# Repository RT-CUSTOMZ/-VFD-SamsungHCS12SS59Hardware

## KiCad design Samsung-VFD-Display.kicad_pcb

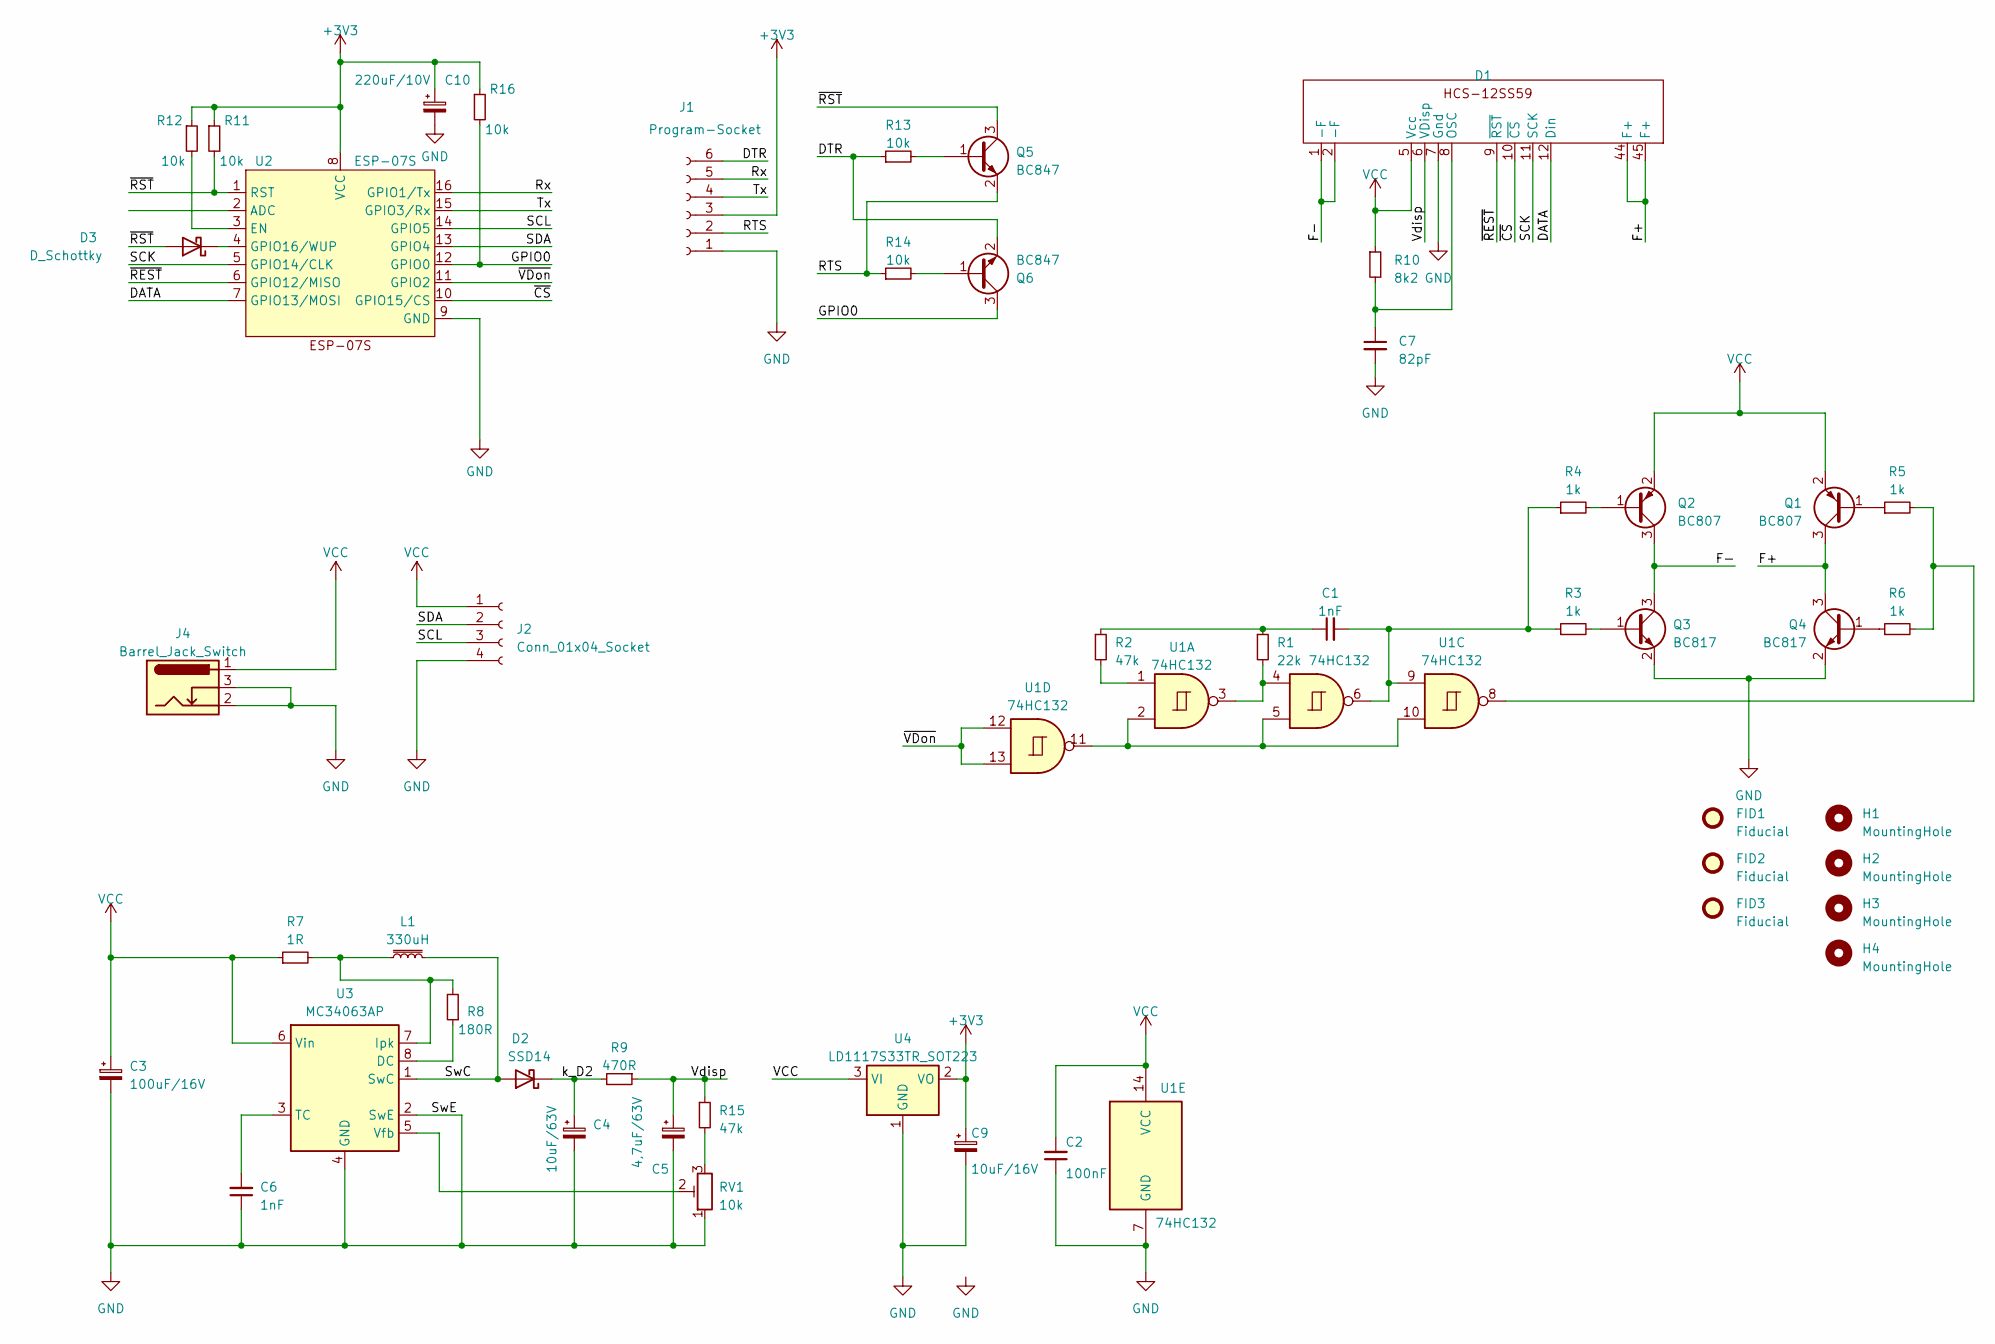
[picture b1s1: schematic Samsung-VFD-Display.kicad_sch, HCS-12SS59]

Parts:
C1, C6: 1nF; C_0805_2012Metric_Pad1.18x1.45mm_HandSolder
C2: 100nF; C_0805_2012Metric_Pad1.18x1.45mm_HandSolder
C3: 100uF/16V; CP_Elec_8x6.9
C4: 10uF/63V; CP_Elec_8x6.9
C5: 4,7uF/63V; CP_Elec_8x6.9
C7: 82pF; C_0805_2012Metric_Pad1.18x1.45mm_HandSolder
C9: 10uF/16V; CP_Elec_8x6.9
C10: 220uF/10V; CP_Elec_8x6.9
D1: HCS-12SS59
D2: SSD14; D_MELF
D3: D_Schottky; D_MiniMELF
FID1, FID2, FID3: Fiducial; Fiducial_1.5mm_Mask3mm
H1, H2, H3, H4: MountingHole; MountingHole_2.7mm_M2.5_DIN965
J1: Program-Socket; PinSocket_1x06_P2.54mm_Vertical
J2: Conn_01x04_Socket; PinSocket_1x04_P2.54mm_Vertical
J4: Barrel_Jack_Switch; BarrelJack_Wuerth_1mm
L1: 330uH; L_Wuerth_WE-PD-Typ-LS
Q1, Q2: BC807; SOT-23
Q3, Q4: BC817; SOT-23
Q5, Q6: BC847; SOT-23
R1: 22k; R_0805_2012Metric_Pad1.20x1.40mm_HandSolder
R2, R15: 47k; R_0805_2012Metric_Pad1.20x1.40mm_HandSolder
R3, R4, R5, R6: 1k; R_0805_2012Metric_Pad1.20x1.40mm_HandSolder
R7: 1R; R_0805_2012Metric_Pad1.20x1.40mm_HandSolder
R8: 180R; R_0805_2012Metric_Pad1.20x1.40mm_HandSolder
R9: 470R; R_0805_2012Metric_Pad1.20x1.40mm_HandSolder
R10: 8k2; R_0805_2012Metric_Pad1.20x1.40mm_HandSolder
R11, R12, R13, R14, R16: 10k; R_0805_2012Metric_Pad1.20x1.40mm_HandSolder
RV1: 10k; Potentiometer_Piher_PT-6-H_Horizontal
U1: 74HC132; SOIC-14_3.9x8.7mm_P1.27mm
U2: ESP-07S; ESP-07_THT
U3: MC34063AP; SOIC-8W_5.3x5.3mm_P1.27mm
U4: LD1117S33TR_SOT223; SOT-223-3_TabPin2

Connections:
+3V3: C9.1, C10.1, J1.3, R11.1, R12.1, R16.1, U2.8 (VCC), U4.2 (VO)
/DATA: D1.12 (Din), U2.7 (GPIO13/MOSI)
/DTR: J1.6, Q6.2 (E), R13.1
/F+: D1.44 (F+), D1.45 (F+), Q1.3 (C), Q4.3 (C)
/F-: D1.1 (-F), D1.2 (-F), Q2.3 (C), Q3.3 (C)
/GPIO0: Q6.3 (C), R16.2, U2.12 (GPIO0)
/RTS: J1.2, Q5.2 (E), R14.1
/Rx: J1.5, U2.16 (GPIO1/Tx)
/SCK: D1.11 (SCK), U2.5 (GPIO14/CLK)
/SCL: J2.3, U2.14 (GPIO5)
/SDA: J2.2, U2.13 (GPIO4)
/SwC: D2.2 (A), L1.2, U3.1 (SwC)
/Tx: J1.4, U2.15 (GPIO3/Rx)
/Vdisp: C5.1, D1.6 (VDisp), R9.1, R15.1
/k_D2: C4.1, D2.1 (K), R9.2
/~CS: D1.10 (~CS), U2.10 (GPIO15/CS)
/~REST: D1.9 (~RST), U2.6 (GPIO12/MISO)
/~RST: D3.2 (A), Q5.3 (C), R11.2, U2.1 (RST)
/~VDon: U1.12, U1.13, U2.11 (GPIO2)
GND: C2.1, C3.2, C4.2, C5.2, C6.1, C7.2, C9.2, C10.2, D1.7 (Gnd), J1.1, J2.4, J4.2, J4.3, Q3.2 (E), Q4.2 (E), RV1.1, U1.7 (GND), U2.9 (GND), U3.2 (SwE), U3.4 (GND), U4.1 (GND)
unnamed: C1.1, R1.1, R2.1
unnamed: C1.2, R3.1, R4.1, U1.6, U1.9
unnamed: C7.1, D1.8 (OSC), R10.2
unnamed: D3.1 (K), U2.4 (GPIO16/WUP)
unnamed: Q1.1 (B), R5.1
unnamed: Q2.1 (B), R4.2
unnamed: Q3.1 (B), R3.2
unnamed: Q4.1 (B), R6.1
unnamed: Q5.1 (B), R13.2
unnamed: Q6.1 (B), R14.2
unnamed: R1.2, U1.3, U1.4
unnamed: R2.2, U1.1
unnamed: R5.2, R6.2, U1.8
unnamed: R15.2, RV1.3
unnamed: U1.2, U1.5, U1.10, U1.11
unnamed: R12.2, U2.3 (EN)
unnamed: R8.1, U3.8 (DC)
unnamed: L1.1, R7.2, R8.2, U3.7 (Ipk)
unnamed: C6.2, U3.3 (TC)
unnamed: RV1.2, U3.5 (Vfb)
VCC: C2.2, C3.1, D1.5 (Vcc), J2.1, J4.1, Q1.2 (E), Q2.2 (E), R7.1, R10.1, U1.14 (VCC), U3.6 (Vin), U4.3 (VI)

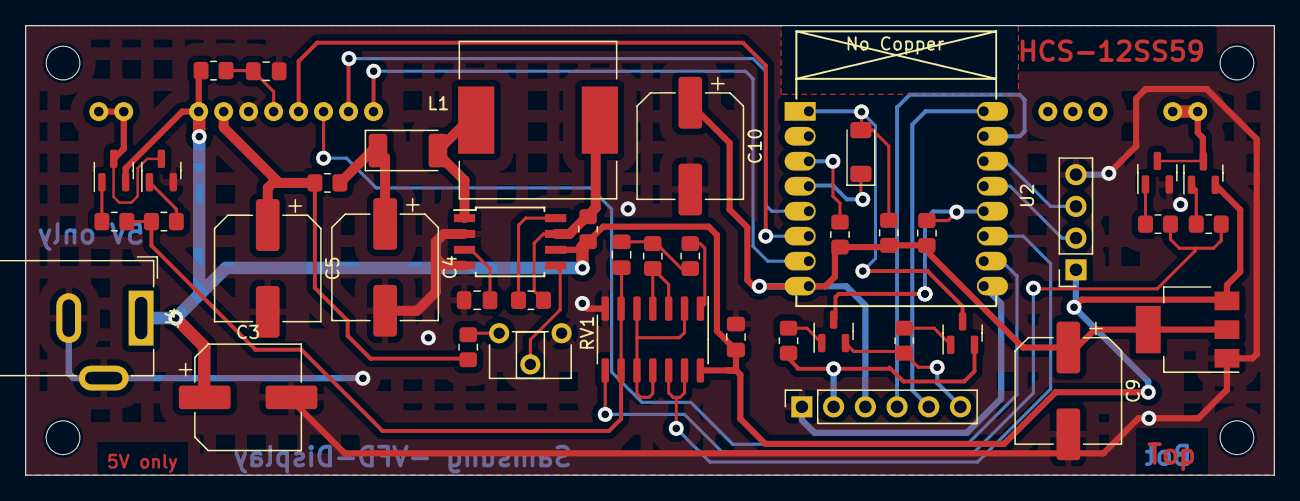
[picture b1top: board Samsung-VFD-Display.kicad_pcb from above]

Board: 2 copper layers, 100.0 x 36.0 mm, 50 parts (1 on the bottom side), 41 nets.

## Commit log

2023-10-26 ESP8266 V01
